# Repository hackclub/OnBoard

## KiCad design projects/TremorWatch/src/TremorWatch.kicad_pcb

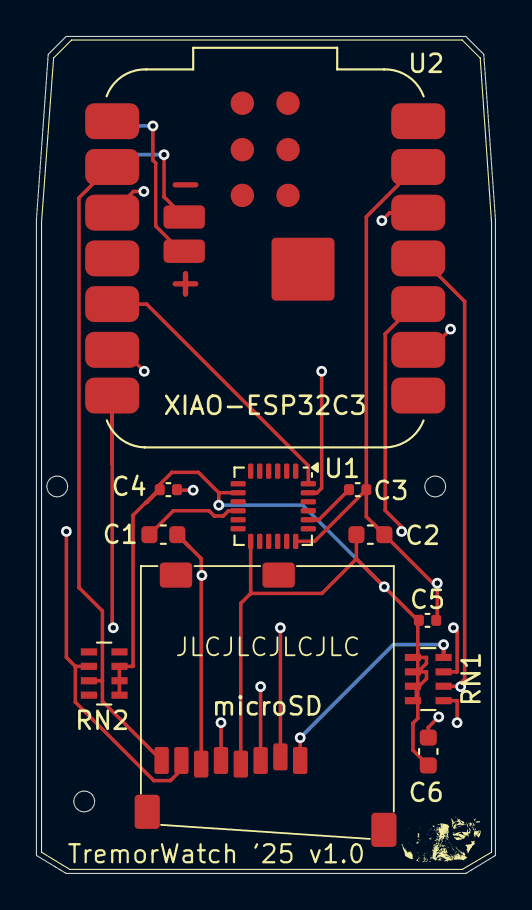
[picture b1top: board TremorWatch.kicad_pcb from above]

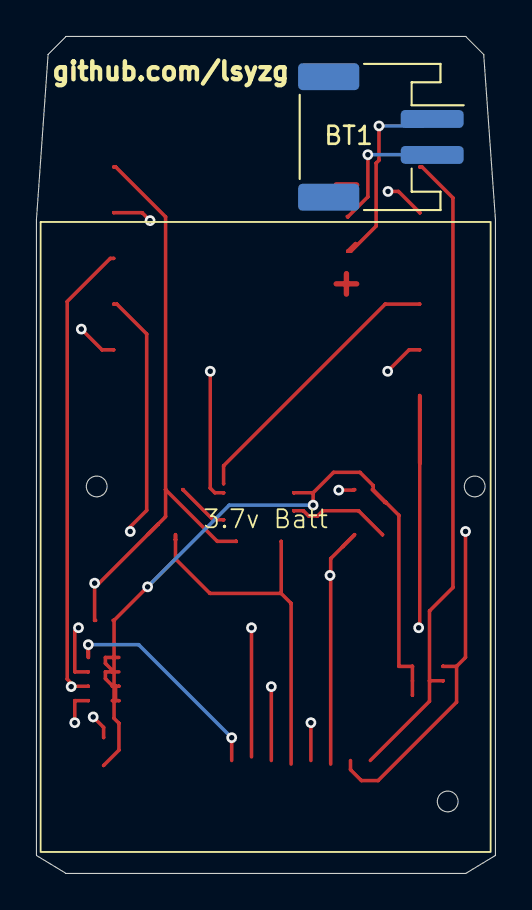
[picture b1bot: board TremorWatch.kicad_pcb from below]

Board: 4 copper layers, 25.5 x 46.5 mm, 14 parts (2 on the bottom side), 14 nets.

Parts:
3.7v Batt: bat_outline
BT1: Battery_Cell; JST_PH_S2B-PH-SM4-TB_1x02-1MP_P2.00mm_Horizontal
C1, C2, C6: 0.1uF; C_0603_1608Metric
C3: 2.2nF; C_0402_1005Metric
C4: 10nF; C_0402_1005Metric
C5: 10uF; C_0402_1005Metric
Intimidator: LOGO; timmy2
RN1, RN2: 4.7k; R_Array_Concave_4x0603
U1: MPU-6050; InvenSense_QFN-24_4x4mm_P0.5mm
U2: XIAO-ESP32C3; MCU_Seeed_ESP32C3
X1: microSD; MicroSD_Socket

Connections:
+3V3: C2.1, C4.1, C5.1, C6.1, RN1.1 (R1.1), RN1.2 (R2.1), RN1.3 (R3.1), RN1.4 (R4.1), RN2.1 (R1.1), RN2.2 (R2.1), RN2.3 (R3.1), U1.8 (VLOGIC), U1.13 (VDD), U2.12 (3V3), X1.4 (SD_VDD)
CLK: RN1.5 (R4.2), U2.9 (PA7_A8_D8_SCK), X1.5 (SCLK)
CS: RN1.7 (R2.2), U2.7 (PB08_A6_D6_TX), X1.2 (CS)
DAT1: RN2.7 (R2.2), U2.2 (PA4_A1_D1), X1.8 (DAT1)
DAT2: RN1.8 (R1.2), U2.3 (PA10_A2_D2), X1.1 (DAT2)
GND: C1.2, C2.2, C3.1, C4.2, C5.2, C6.2, U1.18 (GND), U2.13 (GND), X1.6 (GND@3)
MISO/SO: RN2.6 (R3.2), U2.10 (PA5_A9_D9_MISO), X1.7 (DATA_OUT)
MOSI/SI: RN1.6 (R3.2), U2.11 (PA6_A10_D10_MOSI), X1.3 (DATA_IN)
unnamed: BT1.1 (+), U2.16 (Power_+)
unnamed: BT1.2 (-), U2.17 (Power_-)
unnamed: C3.2, U1.20 (CPOUT)
unnamed: C1.1, U1.10 (REGOUT)
SCL: U1.23 (SCL), U2.6 (PA9_A5_D5_SCL)
SDA: U1.24 (SDA), U2.5 (PA8_A4_D4_SDA)

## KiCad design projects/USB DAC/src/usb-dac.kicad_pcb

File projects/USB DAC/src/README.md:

# usb-dac

USB DAC based on TI PCM2912A IC

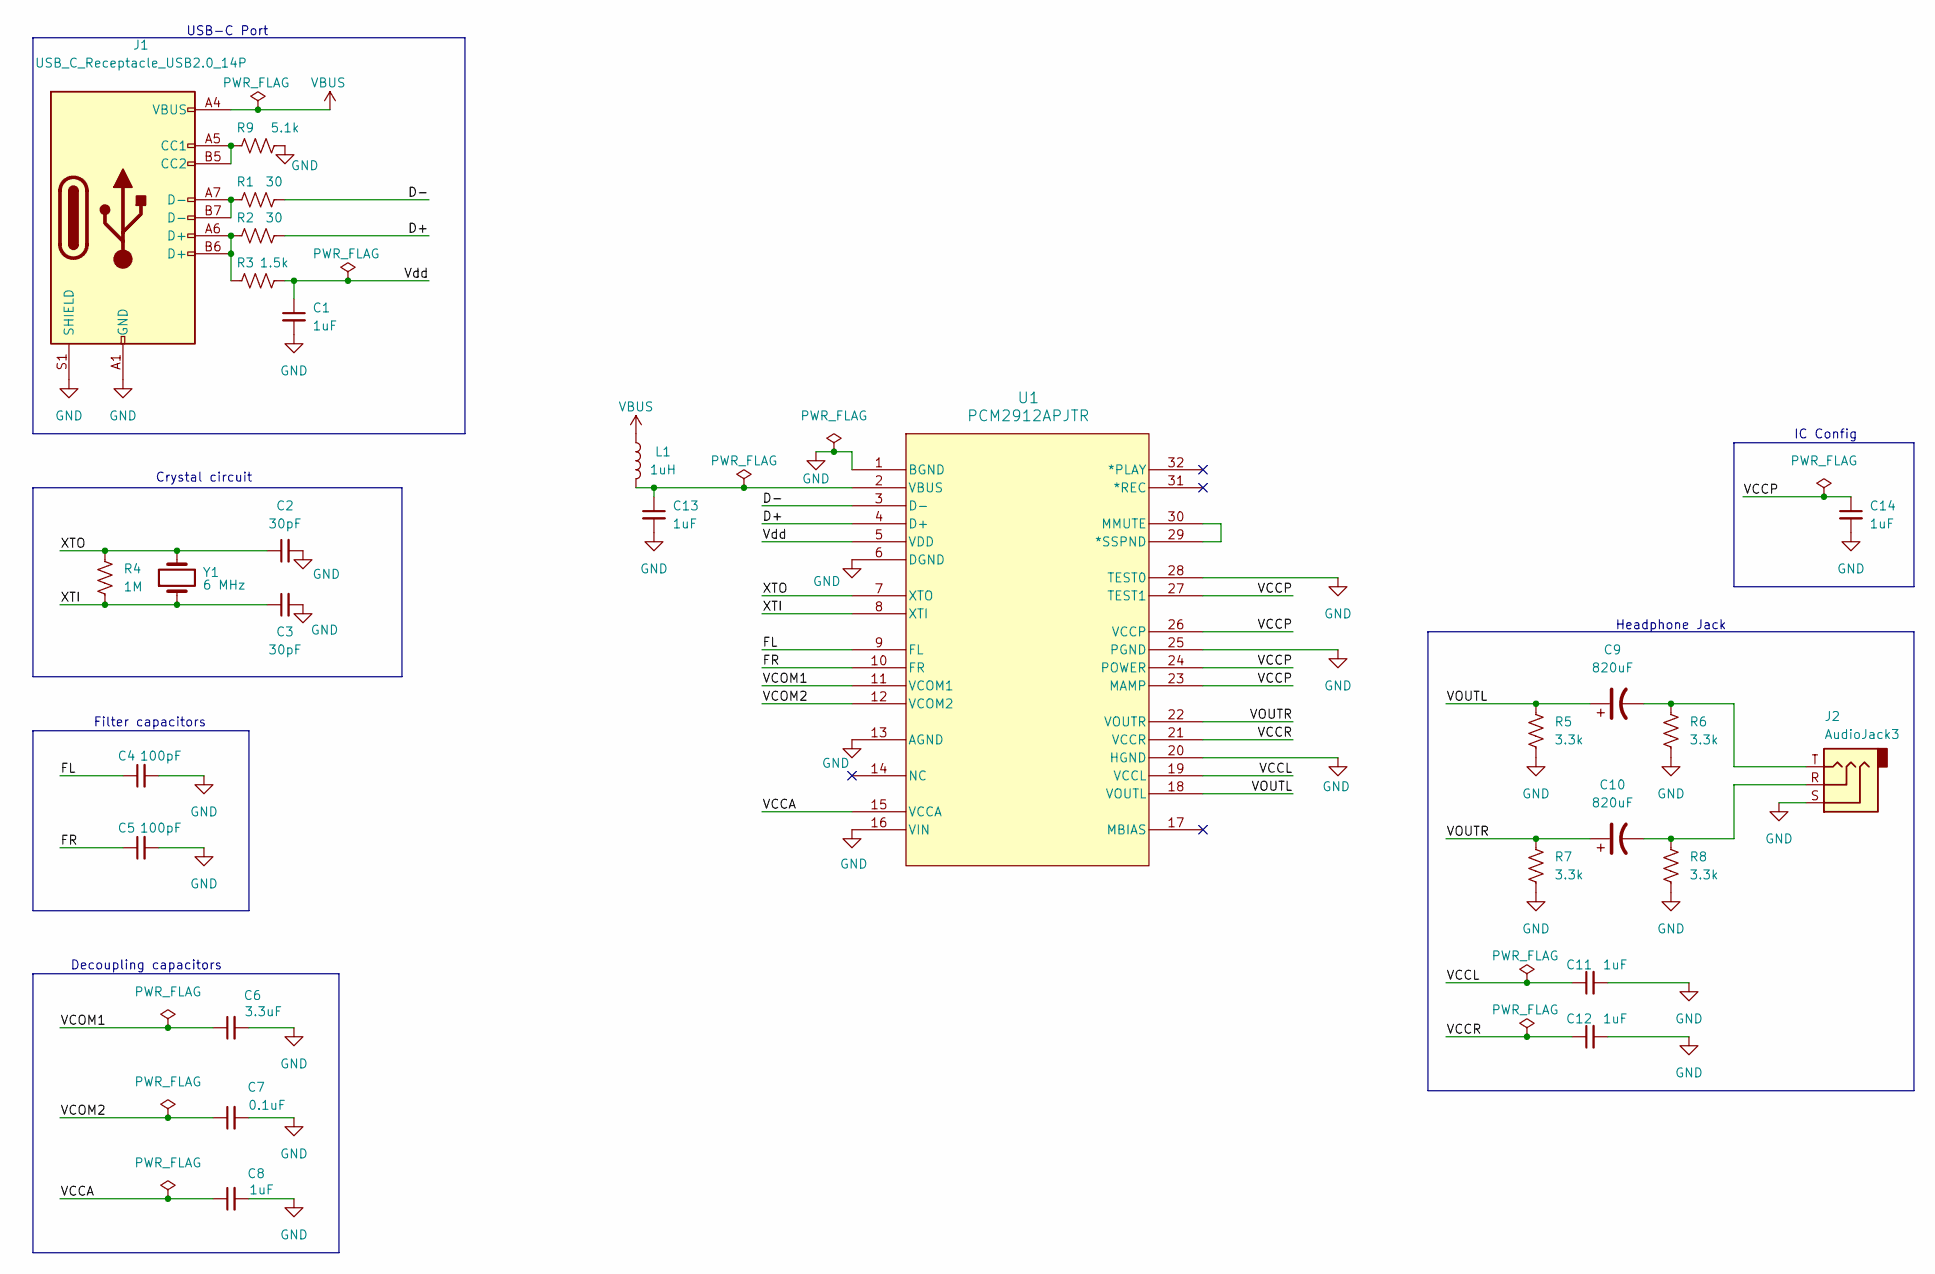
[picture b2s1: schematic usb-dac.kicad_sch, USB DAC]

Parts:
C1, C8, C11, C12, C13, C14: 1uF; C_Rect_L7.0mm_W2.0mm_P5.00mm; Mfr. # FG28X7R1E105KRT00
C2, C3: 30pF; C_Rect_L7.0mm_W2.0mm_P5.00mm; Mfr. # K300J10C0GF5UH5
C4, C5: 100pF; C_Rect_L7.0mm_W2.0mm_P5.00mm; Mfr. # XR501101K040HAND5P
C6: 3.3uF; C_Rect_L7.0mm_W2.0mm_P5.00mm; Mfr. # FA24X7R1E335KRU06
C7: 0.1uF; C_Rect_L7.0mm_W2.0mm_P5.00mm; Mfr. # K104K10X7RF5UH5
C9, C10: 820uF; CP_Radial_D8.0mm_P3.50mm; Mfr. # 6.3ZLH820MEFC8X11.5
J1: USB_C_Receptacle_USB2.0_14P; USB_C_Receptacle_GCT_USB4105-xx-A_16P_TopMnt_Horizontal; Mfr. # USB4085
J2: AudioJack3; Jack_3.5mm_CUI_SJ1-3523N_Horizontal; Mfr. # SJ1-3523N
L1: 1uH; L_Axial_L5.3mm_D2.2mm_P7.62mm_Horizontal_Vishay_IM-1; Mfr. # AICC-02-1R0M-T
R1, R2: 30; R_Axial_DIN0207_L6.3mm_D2.5mm_P10.16mm_Horizontal; Mfr. # CF14JT30R0
R3: 1.5k; R_Axial_DIN0207_L6.3mm_D2.5mm_P10.16mm_Horizontal; Mfr. # CFR-12JB-52-1K5
R4: 1M; R_Axial_DIN0207_L6.3mm_D2.5mm_P10.16mm_Horizontal; Mfr. # RNF18FTD1M00
R5, R6, R7, R8: 3.3k; R_Axial_DIN0207_L6.3mm_D2.5mm_P10.16mm_Horizontal; Mfr. # CFM14JT3K30
R9: 5.1k; R_Axial_DIN0207_L6.3mm_D2.5mm_P10.16mm_Horizontal; Mfr. # CF18JT5K10
U1: PCM2912APJTR; TQFP-32_7x7mm_P0.8mm; Mfr. # PCM2912APJTR
Y1: 6 MHz; Crystal_HC49-U_Vertical; Mfr. # ATS060

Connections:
/D+: R2.2, U1.4 (D+)
/D-: R1.2, U1.3 (D-)
/FL: C4.1, U1.9 (FL)
/FR: C5.1, U1.10 (FR)
/VCCA: C8.1, U1.15 (VCCA)
/VCCL: C11.1, U1.19 (VCCL)
/VCCP: C14.1, U1.23 (MAMP), U1.24 (POWER), U1.26 (VCCP), U1.27 (TEST1)
/VCCR: C12.1, U1.21 (VCCR)
/VCOM1: C6.1, U1.11 (VCOM1)
/VCOM2: C7.1, U1.12 (VCOM2)
/VOUTL: C9.1, R5.1, U1.18 (VOUTL)
/VOUTR: C10.1, R7.1, U1.22 (VOUTR)
/Vdd: C1.1, R3.2, U1.5 (VDD)
/XTI: C3.1, R4.2, U1.8 (XTI), Y1.1
/XTO: C2.1, R4.1, U1.7 (XTO), Y1.2
GND: C1.2, C2.2, C3.2, C4.2, C5.2, C6.2, C7.2, C8.2, C11.2, C12.2, C13.2, C14.2, J1.A1 (GND), J1.A12 (GND), J1.B1 (GND), J1.B12 (GND), J1.S1 (SHIELD), J2.S, R5.2, R6.2, R7.2, R8.2, R9.2, U1.1 (BGND), U1.6 (DGND), U1.13 (AGND), U1.16 (VIN), U1.20 (HGND), U1.25 (PGND), U1.28 (TEST0)
unnamed: C9.2, J2.T, R6.1
unnamed: C10.2, J2.R, R8.1
unnamed: J1.A5 (CC1), J1.B5 (CC2), R9.1
unnamed: J1.A6 (D+), J1.B6 (D+), R2.1, R3.1
unnamed: J1.A7 (D-), J1.B7 (D-), R1.1
unnamed: U1.29 (*SSPND), U1.30 (MMUTE)
unnamed: C13.1, L1.2, U1.2 (VBUS)
VBUS: J1.A4 (VBUS), J1.A9 (VBUS), J1.B4 (VBUS), J1.B9 (VBUS), L1.1

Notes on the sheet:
Filter capacitors
Headphone Jack
USB-C Port
Crystal circuit
Decoupling capacitors
IC Config

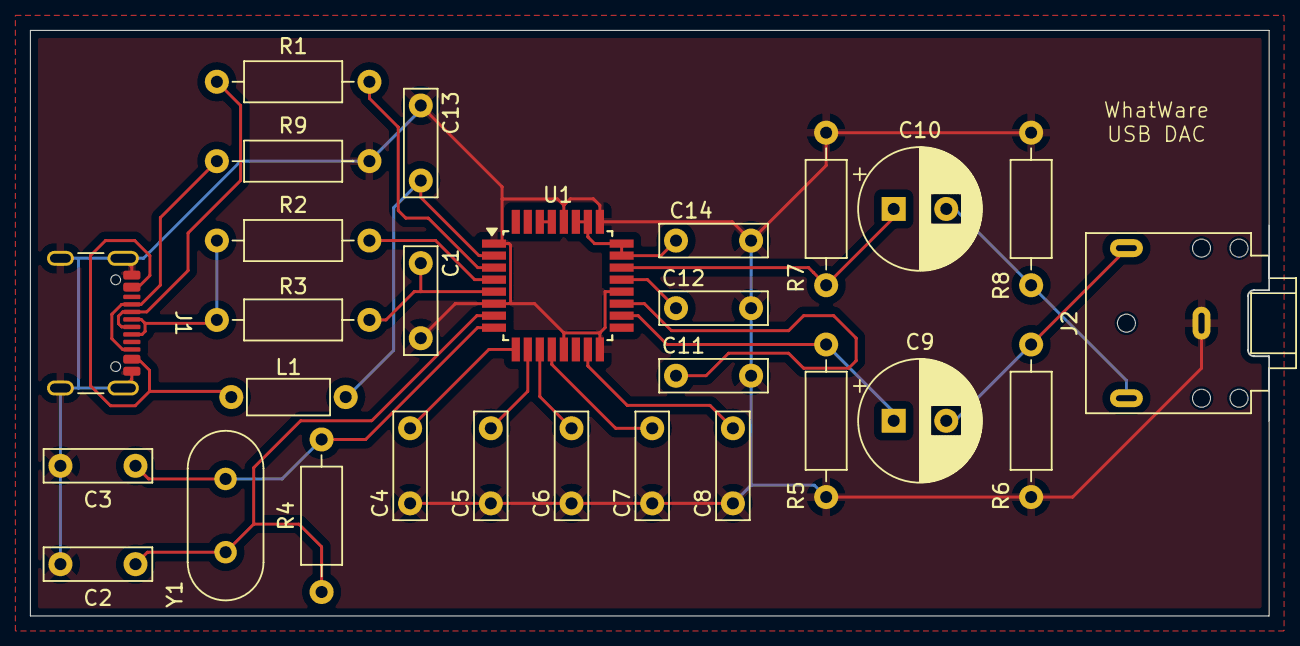
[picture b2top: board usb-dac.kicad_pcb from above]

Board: 2 copper layers, 82.5 x 39.0 mm, 28 parts (0 on the bottom side), 24 nets.

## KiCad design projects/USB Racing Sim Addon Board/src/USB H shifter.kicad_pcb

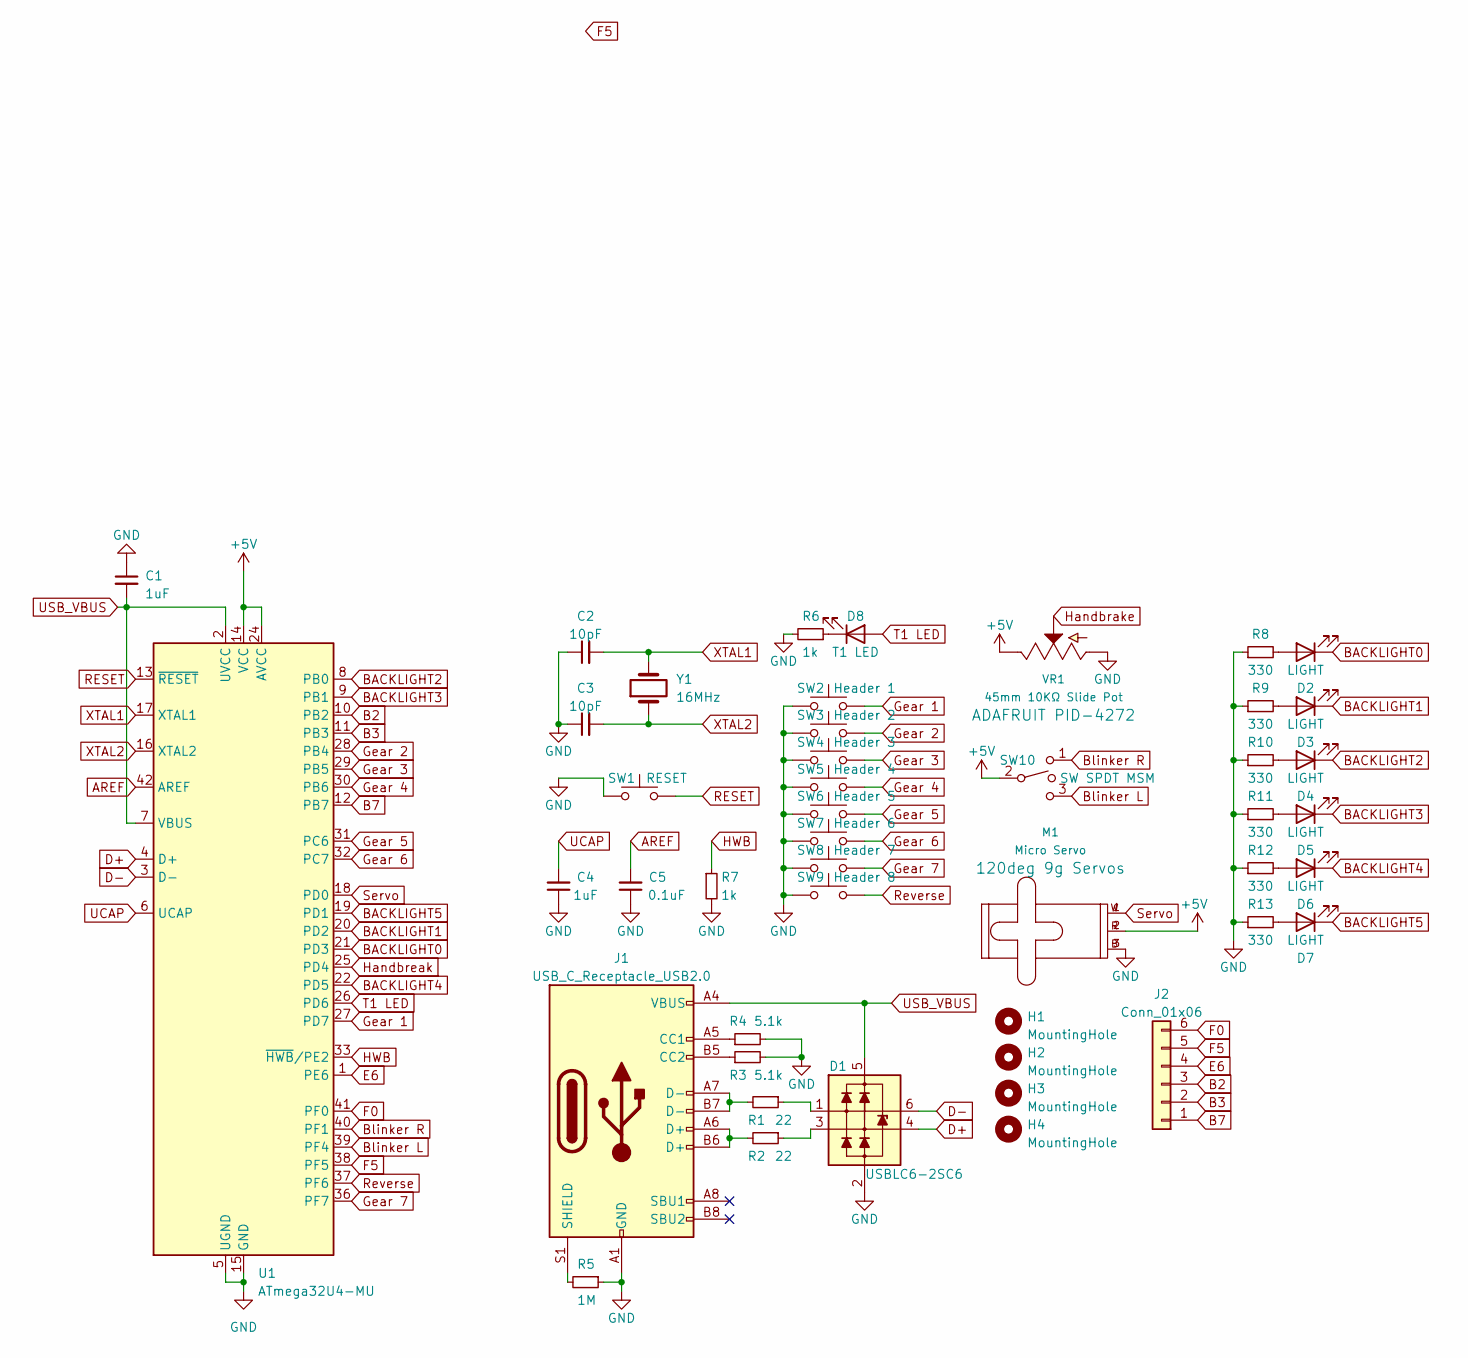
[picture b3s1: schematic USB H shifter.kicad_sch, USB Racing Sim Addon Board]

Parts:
C1, C4: 1uF; C_Disc_D4.3mm_W1.9mm_P5.00mm
C2, C3: 10pF; C_Disc_D3.0mm_W2.0mm_P2.50mm
C5: 0.1uF; C_Disc_D3.0mm_W2.0mm_P2.50mm
D1: USBLC6-2SC6; SOT-23-6
D2, D3, D4, D5, D6, D7: LIGHT; LED_D3.0mm
D8: T1 LED; LED_D3.0mm
H1, H2, H3, H4: MountingHole; MountingHole_2.2mm_M2
J1: USB_C_Receptacle_USB2.0; USB_C_Receptacle_Palconn_UTC16-G
J2: Conn_01x06; PinHeader_2x03_P2.54mm_Vertical
M1: Micro Servo; PinHeader_1x03_P2.54mm_Vertical
R1, R2: 22; R_0603_1608Metric
R3, R4: 5.1k; R_0603_1608Metric
R5: 1M; R_0603_1608Metric
R6, R7: 1k; R_0603_1608Metric
R8, R9, R10, R11, R12, R13: 330; R_0603_1608Metric
SW1: RESET; SW_PUSH_6mm
SW2: Header 1; PinHeader_1x02_P2.54mm_Vertical
SW3: Header 2; PinHeader_1x02_P2.54mm_Vertical
SW4: Header 3; PinHeader_1x02_P2.54mm_Vertical
SW5: Header 4; PinHeader_1x02_P2.54mm_Vertical
SW6: Header 5; PinHeader_1x02_P2.54mm_Vertical
SW7: Header 6; PinHeader_1x02_P2.54mm_Vertical
SW8: Header 7; PinHeader_1x02_P2.54mm_Vertical
SW9: Header 8; PinHeader_1x02_P2.54mm_Vertical
SW10: SW SPDT MSM; PinHeader_1x03_P2.54mm_Vertical
U1: ATmega32U4-MU; TQFP-44_10x10mm_P0.8mm
VR1: 45mm 10KΩ Slide Pot; PinHeader_1x03_P2.54mm_Vertical
Y1: 16MHz; Crystal_HC49-4H_Vertical

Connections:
+5V: M1.2 (V+), SW10.2, U1.14 (VCC), U1.24 (AVCC), U1.34 (VCC), U1.44 (AVCC), VR1.1 (E)
AREF: C5.2, U1.42 (AREF)
B2: J2.3, U1.10 (PB2)
B3: J2.2, U1.11 (PB3)
B7: J2.1, U1.12 (PB7)
BACKLIGHT0: D2.1 (K), U1.21 (PD3)
BACKLIGHT1: D3.1 (K), U1.20 (PD2)
BACKLIGHT2: D4.1 (K), U1.8 (PB0)
BACKLIGHT3: D5.1 (K), U1.9 (PB1)
BACKLIGHT4: D6.1 (K), U1.22 (PD5)
BACKLIGHT5: D7.1 (K), U1.19 (PD1)
Blinker L: SW10.3, U1.39 (PF4)
Blinker R: SW10.1, U1.40 (PF1)
D+: D1.4 (L2), U1.4 (D+)
D-: D1.6 (L1), U1.3 (D-)
E6: J2.4, U1.1 (PE6)
F0: J2.6, U1.41 (PF0)
F5: J2.5, U1.38 (PF5)
GND: C1.1, C2.1, C3.1, C4.1, C5.1, D1.2 (VN), J1.A1 (GND), J1.A12 (GND), J1.B1 (GND), J1.B12 (GND), M1.3 (GND), R3.2, R4.2, R5.1, R6.2, R7.2, R8.1, R9.1, R10.1, R11.1, R12.1, R13.1, SW1.1, SW2.1, SW3.1, SW4.1, SW5.1, SW6.1, SW7.1, SW8.1, SW9.1, U1.5 (UGND), U1.15 (GND), U1.23 (GND), U1.35 (GND), U1.43 (GND), VR1.3 (A)
Gear 1: SW2.2, U1.27 (PD7)
Gear 2: SW3.2, U1.28 (PB4)
Gear 3: SW4.2, U1.29 (PB5)
Gear 4: SW5.2, U1.30 (PB6)
Gear 5: SW6.2, U1.31 (PC6)
Gear 6: SW7.2, U1.32 (PC7)
Gear 7: SW8.2, U1.36 (PF7)
HWB: R7.1, U1.33 (~HWB/PE2)
Handbreak: U1.25 (PD4), VR1.2
unnamed: D1.1 (L1), R1.1
unnamed: D1.3 (L2), R2.1
unnamed: D2.2 (A), R8.2
unnamed: D3.2 (A), R9.2
unnamed: D4.2 (A), R10.2
unnamed: D5.2 (A), R11.2
unnamed: D6.2 (A), R12.2
unnamed: D7.2 (A), R13.2
unnamed: D8.1 (K), R6.1
unnamed: J1.A5 (CC1), R4.1
unnamed: J1.B5 (CC2), R3.1
unnamed: J1.A6 (D+), J1.B6 (D+), R2.2
unnamed: J1.A7 (D-), J1.B7 (D-), R1.2
unnamed: J1.S1 (SHIELD), R5.2
RESET: SW1.2, U1.13 (~RESET)
Reverse: SW9.2, U1.37 (PF6)
Servo: M1.1 (SIG), U1.18 (PD0)
T1 LED: D8.2 (A), U1.26 (PD6)
UCAP: C4.2, U1.6 (UCAP)
USB_VBUS: C1.2, D1.5 (VP), J1.A4 (VBUS), J1.A9 (VBUS), J1.B4 (VBUS), J1.B9 (VBUS), U1.2 (UVCC), U1.7 (VBUS)
XTAL1: C2.2, U1.17 (XTAL1), Y1.2
XTAL2: C3.2, U1.16 (XTAL2), Y1.1

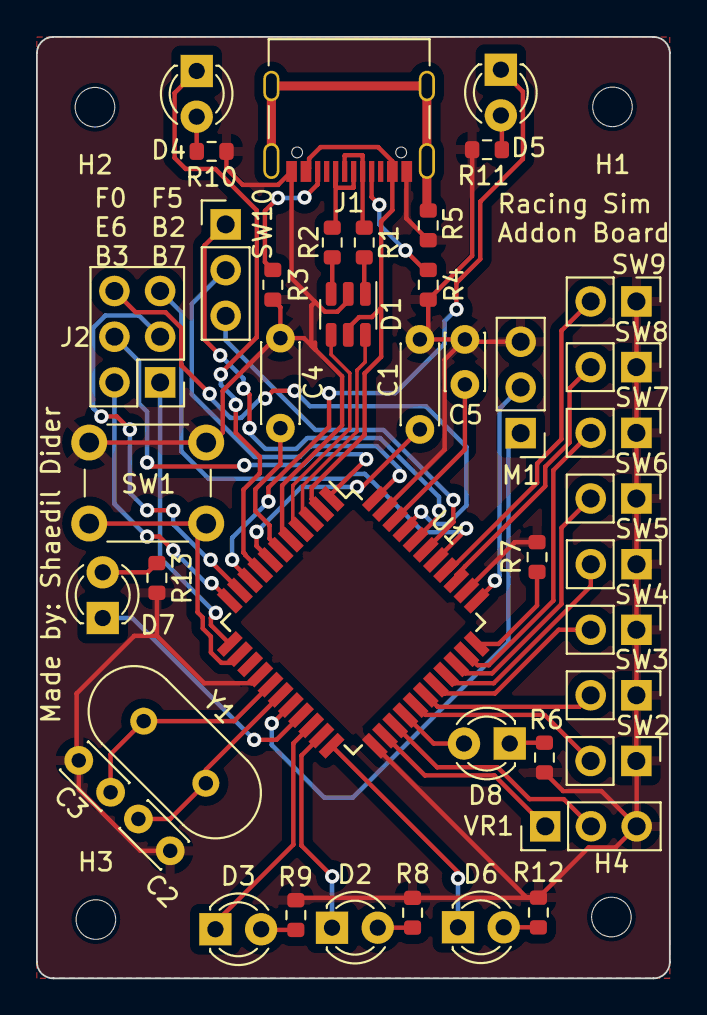
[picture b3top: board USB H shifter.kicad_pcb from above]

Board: 2 copper layers, 35.2 x 52.3 mm, 46 parts (0 on the bottom side), 50 nets.

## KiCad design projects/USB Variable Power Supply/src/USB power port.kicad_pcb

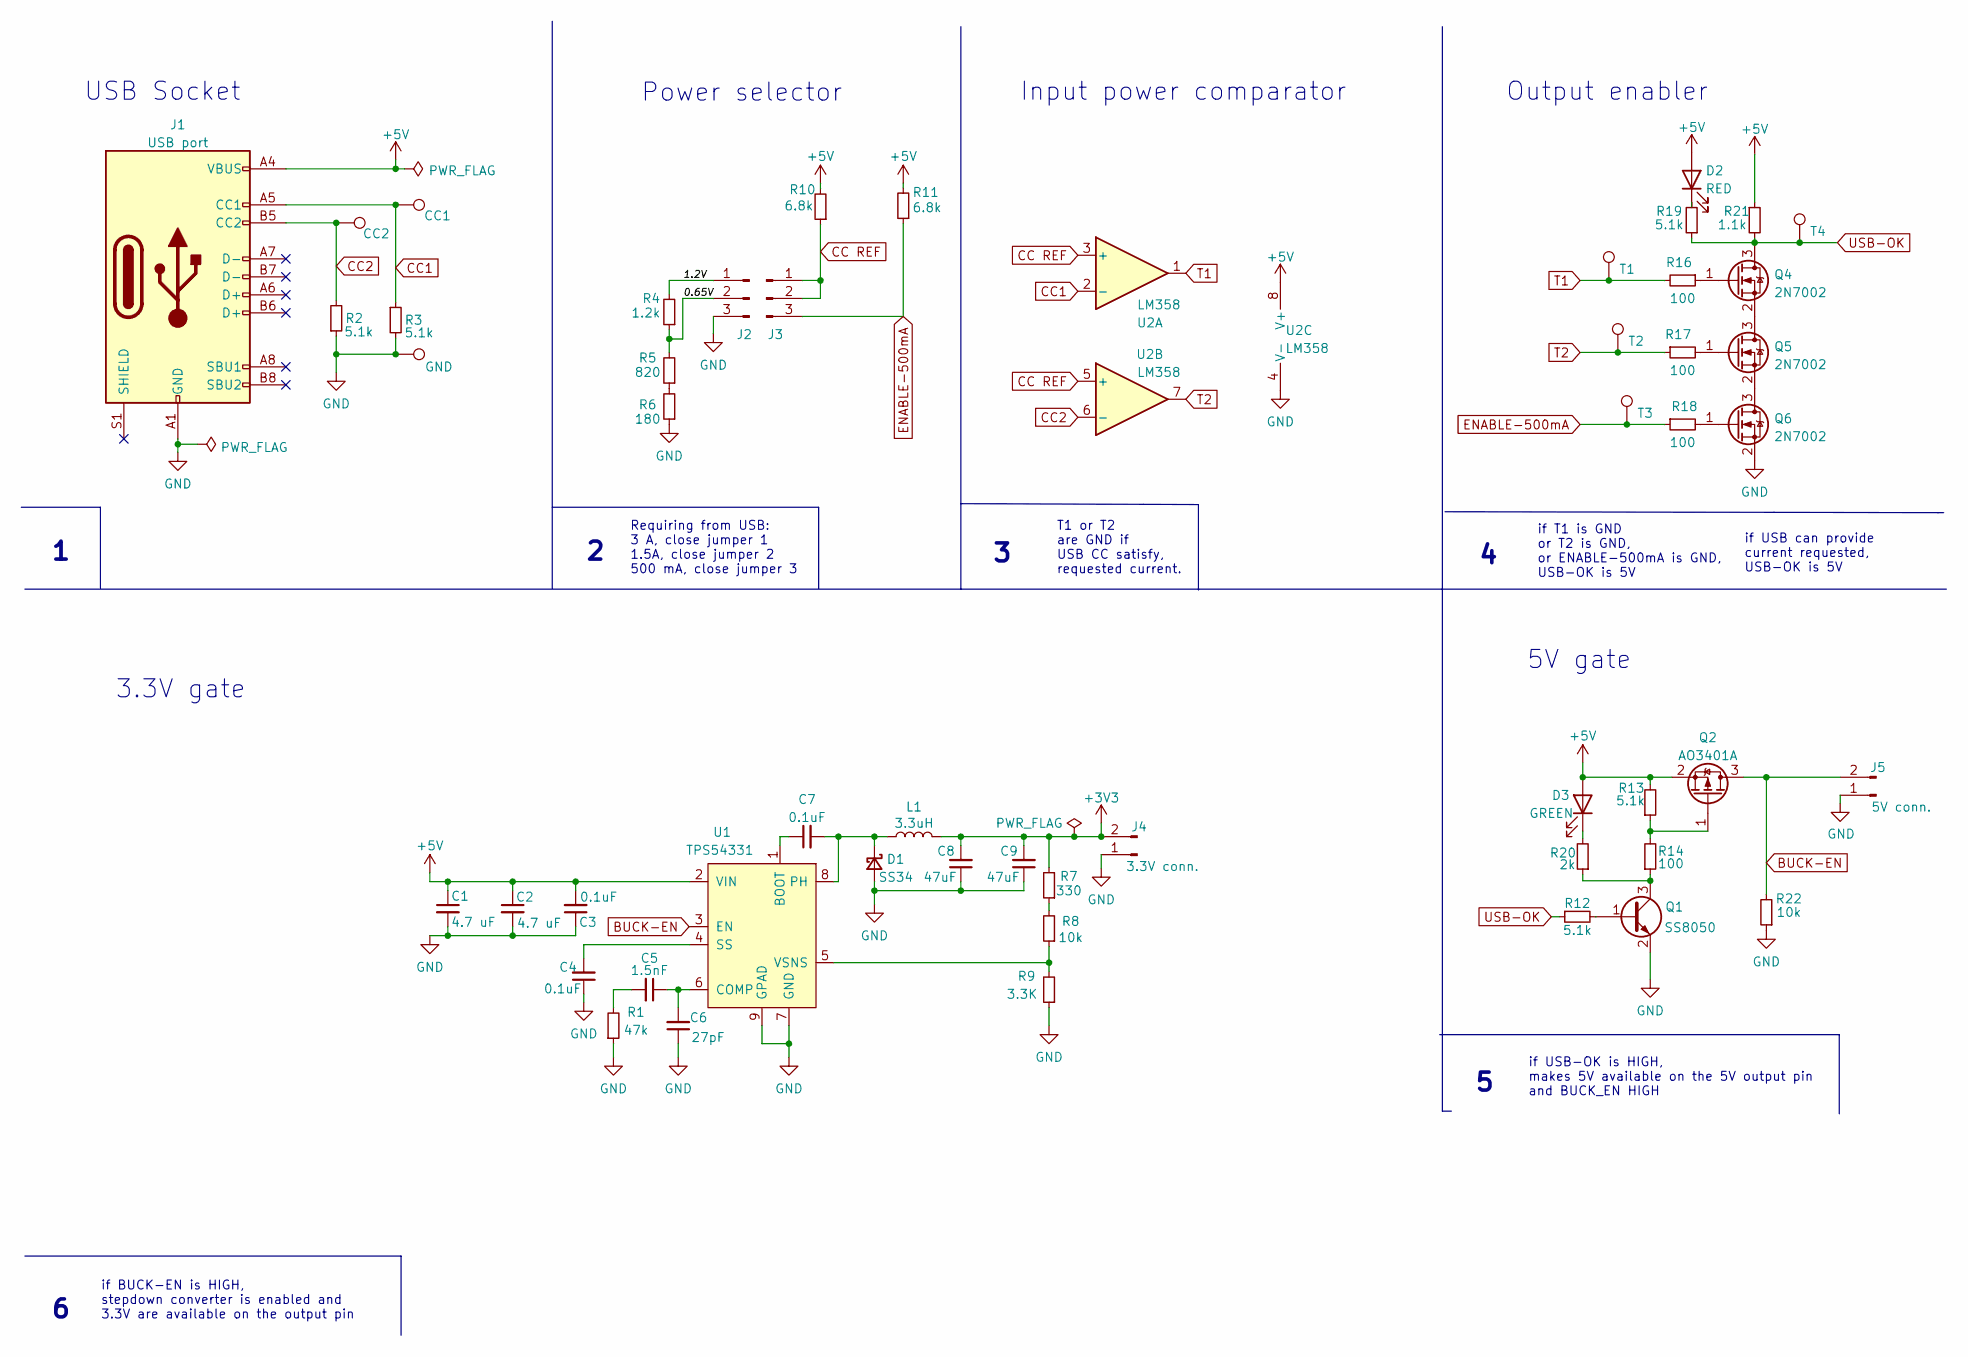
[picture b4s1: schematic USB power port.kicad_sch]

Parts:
C1, C2: 4.7 uF; C_1206_3216Metric; PartNo C29823
C3, C4, C7: 0.1uF; C_0603_1608Metric; PartNo C14663
C5: 1.5nF; C_0603_1608Metric; PartNo C1595
C6: 27pF; C_0603_1608Metric; PartNo C107045
C8, C9: 47uF; C_1206_3216Metric; PartNo C96123
D1: SS34; D_SMA; PartNo C8678
D2: RED; LED_0603_1608Metric; PartNo C2286
D3: GREEN; LED_0603_1608Metric; PartNo C72043
J1: USB port; USB_C_Receptacle_XKB_U262-16XN-4BVC11; PartNo C319148
J2, J3: Selector; PinHeader_1x03_P2.54mm_Vertical
J4: 3.3V conn.; PinHeader_1x02_P2.54mm_Vertical
J5: 5V conn.; PinHeader_1x02_P2.54mm_Vertical
L1: 3.3uH; MWSA0402; PartNo C285742
Q1: SS8050; SOT-23; PartNo C2150
Q2: AO3401A; SOT-23; PartNo C15127
Q4, Q5, Q6: 2N7002; SOT-23; PartNo C8545
R1: 47k; R_0603_1608Metric; PartNo C25819
R2, R3, R12, R13, R19: 5.1k; R_0603_1608Metric; PartNo C23186
R4: 1.2k; R_0603_1608Metric; PartNo C22765
R5: 820; R_0603_1608Metric; PartNo C23253
R6: 180; R_0603_1608Metric; PartNo C22828
R7: 330; R_0603_1608Metric; PartNo C23138
R8, R22: 10k; R_0603_1608Metric; PartNo C25804
R9: 3.3K; R_0603_1608Metric; PartNo C22978
R10, R11: 6.8k; R_0603_1608Metric; PartNo C23212
R14, R16, R17, R18: 100; R_0603_1608Metric; PartNo C22775
R20: 2k; R_0603_1608Metric; PartNo C22975
R21: 1.1k; R_0603_1608Metric; PartNo C22764
TP1: CC2; TestPoint_THTPad_D2.0mm_Drill1.0mm
TP2: CC1; TestPoint_THTPad_D2.0mm_Drill1.0mm
TP3: GND; TestPoint_THTPad_2.0x2.0mm_Drill1.0mm
TP4: T1; TestPoint_THTPad_D2.0mm_Drill1.0mm
TP5: T2; TestPoint_THTPad_D2.0mm_Drill1.0mm
TP6: T3; TestPoint_THTPad_D2.0mm_Drill1.0mm
TP7: T4; TestPoint_THTPad_D2.0mm_Drill1.0mm
U1: TPS54331; TI_SO-PowerPAD-8_ThermalVias; PartNo C9865
U2: LM358; SOIC-8_3.9x4.9mm_P1.27mm; PartNo C7950

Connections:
+3V3: C8.2, C9.2, J4.2, L1.2, R7.2
+5V: C1.1, C2.1, C3.2, D2.2 (A), D3.2 (A), J1.A4 (VBUS), J1.A9 (VBUS), J1.B4 (VBUS), J1.B9 (VBUS), Q2.2 (S), R10.2, R11.2, R13.2, R21.1, U1.2 (VIN), U2.8 (V+)
/0.65V: J2.2, R4.1, R5.2
/1.2V: J2.1, R4.2
BUCK-EN: J5.2, Q2.3 (D), R22.2, U1.3 (EN)
CC1: J1.A5 (CC1), R3.1, TP2.1, U2.2 (-)
CC2: J1.B5 (CC2), R2.2, TP1.1, U2.6 (-)
CC REF: J3.1, J3.2, R10.1, U2.3 (+), U2.5 (+)
ENABLE-500mA: J3.3, R11.1, R18.1, TP6.1
GND: C1.2, C2.2, C3.1, C4.1, C6.1, C8.1, C9.1, D1.2 (A), J1.A1 (GND), J1.A12 (GND), J1.B1 (GND), J1.B12 (GND), J2.3, J4.1, J5.1, Q1.2 (E), Q6.2 (S), R1.1, R2.1, R3.2, R6.1, R9.1, R22.1, TP3.1, U1.7 (GND), U1.9 (GPAD), U2.4 (V-)
unnamed: C5.2, R1.2
unnamed: C7.2, D1.1 (K), L1.1, U1.8 (PH)
unnamed: D2.1 (K), R19.2
unnamed: D3.1 (K), R20.2
unnamed: Q1.1 (B), R12.2
unnamed: Q1.3 (C), R14.1, R20.1
unnamed: Q2.1 (G), R13.1, R14.2
unnamed: Q4.1 (G), R16.1
unnamed: Q4.2 (S), Q5.3 (D)
unnamed: Q5.1 (G), R17.2
unnamed: Q5.2 (S), Q6.3 (D)
unnamed: Q6.1 (G), R18.2
unnamed: R5.1, R6.2
unnamed: R7.1, R8.2
unnamed: C7.1, U1.1 (BOOT)
unnamed: C5.1, C6.2, U1.6 (COMP)
unnamed: C4.2, U1.4 (SS)
unnamed: R8.1, R9.2, U1.5 (VSNS)
T1: R16.2, TP4.1, U2.1
T2: R17.1, TP5.1, U2.7
USB-OK: Q4.3 (D), R12.1, R19.1, R21.2, TP7.1

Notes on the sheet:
Input power comparator
if BUCK-EN is HIGH, stepdown converter is enabled and 3.3V are available on the output pin
if USB-OK is HIGH, makes 5V available on the 5V output pin and BUCK_EN HIGH
USB Socket
Output enabler
if USB can provide current requested, USB-OK is 5V
if T1 is GND or T2 is GND, or ENABLE-500mA is GND, USB-OK is 5V
T1 or T2 are GND if USB CC satisfy, requested current.
Power selector
Requiring from USB: 3 A, close jumper 1 1.5A, close jumper 2 500 mA, close jumper 3
5V gate
3.3V gate

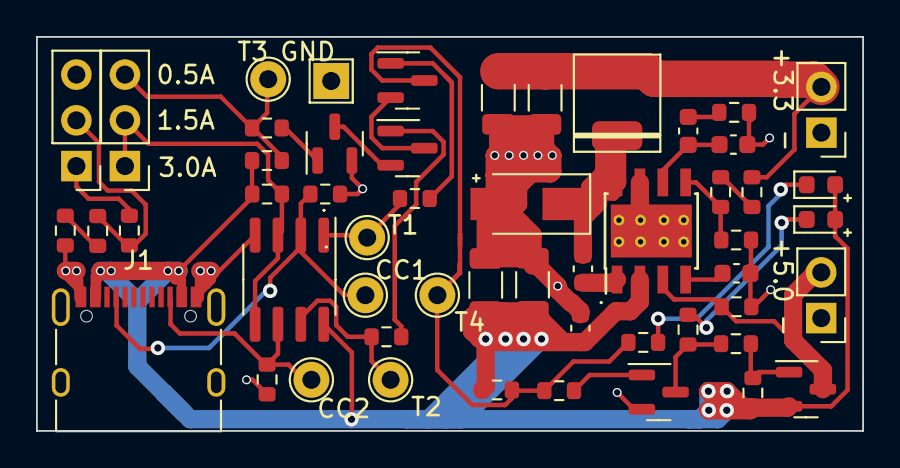
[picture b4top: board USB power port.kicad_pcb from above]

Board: 2 copper layers, 45.9 x 21.9 mm, 53 parts (0 on the bottom side), 31 nets.

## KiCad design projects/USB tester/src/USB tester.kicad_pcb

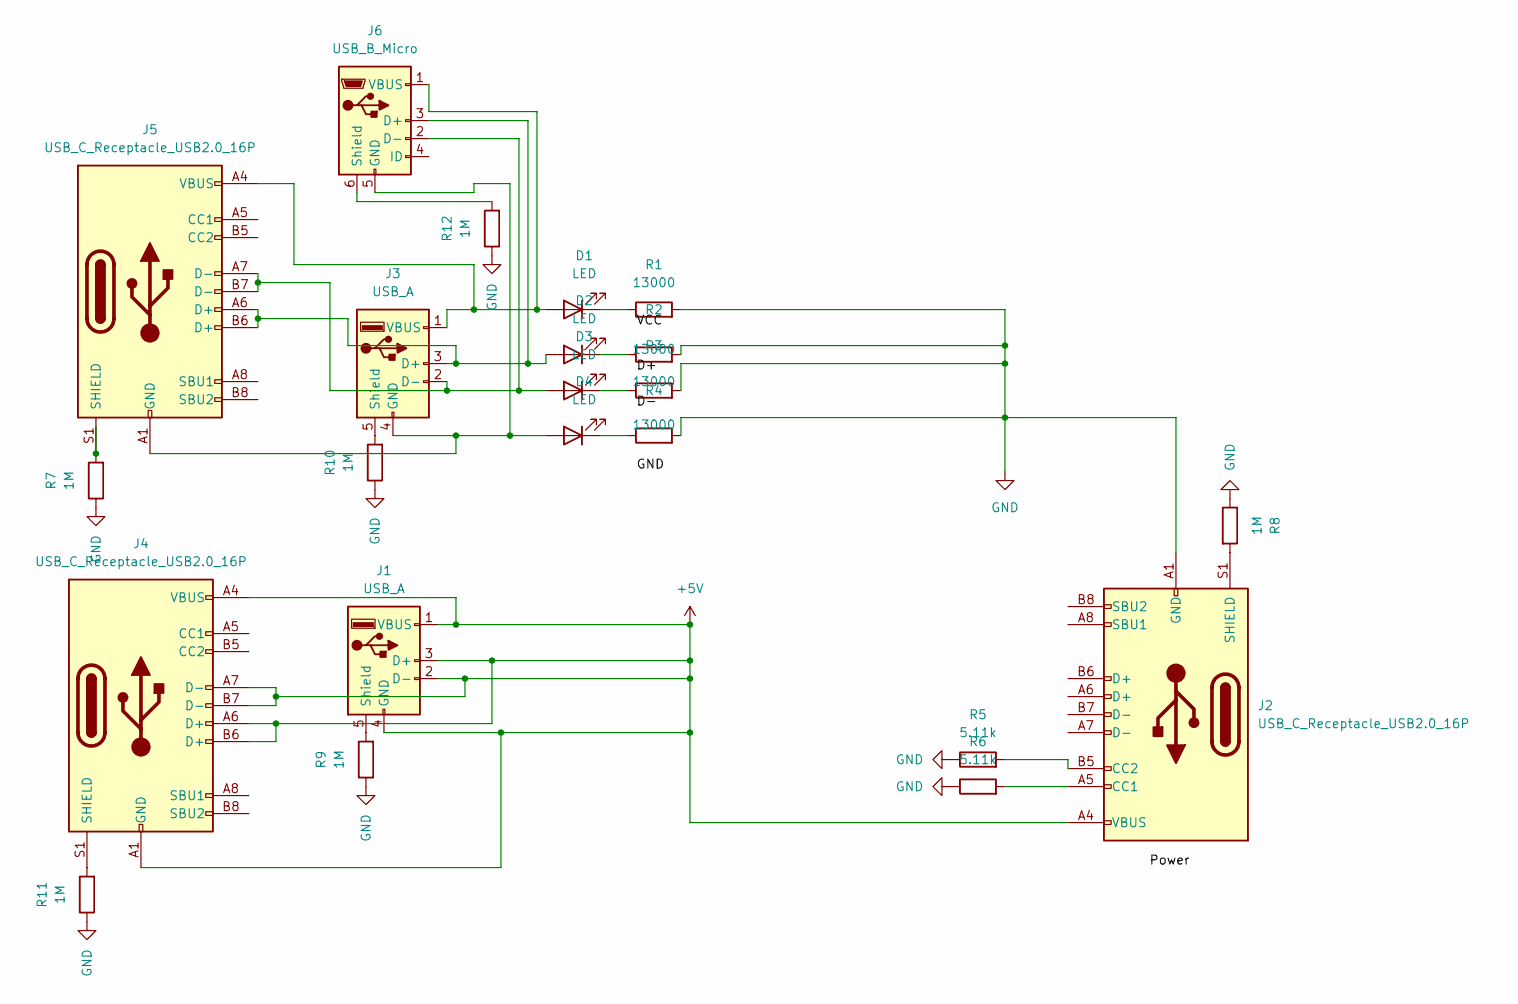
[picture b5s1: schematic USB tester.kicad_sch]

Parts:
D1, D2, D3, D4: LED; LED_1206_3216Metric
J1, J3: USB_A; USB_A_Receptacle_GCT_USB1046
J2, J4, J5: USB_C_Receptacle_USB2.0_16P; USB_C_Receptacle_G-Switch_GT-USB-7010ASV
J6: USB_B_Micro; USB_Micro-AB_Molex_47590-0001
R1, R2, R3, R4: 13000; R_0805_2012Metric
R5, R6: 5.11k; R_0805_2012Metric
R7, R8, R9, R10, R11, R12: 1M; R_0805_2012Metric

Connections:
+5V: J1.1 (VBUS), J1.2 (D-), J1.3 (D+), J1.4 (GND), J2.A4 (VBUS), J2.A9 (VBUS), J2.B4 (VBUS), J2.B9 (VBUS), J4.A1 (GND), J4.A4 (VBUS), J4.A6 (D+), J4.A7 (D-), J4.A9 (VBUS), J4.A12 (GND), J4.B1 (GND), J4.B4 (VBUS), J4.B6 (D+), J4.B7 (D-), J4.B9 (VBUS), J4.B12 (GND)
GND: J2.A1 (GND), J2.A12 (GND), J2.B1 (GND), J2.B12 (GND), R1.2, R2.2, R3.2, R4.2, R5.1, R6.1, R7.1, R8.1, R9.1, R10.1, R11.1, R12.1
unnamed: D1.2 (A), J3.1 (VBUS), J5.A4 (VBUS), J5.A9 (VBUS), J5.B4 (VBUS), J5.B9 (VBUS), J6.1 (VBUS)
unnamed: D1.1 (K), R1.1
unnamed: D2.2 (A), J3.3 (D+), J5.A6 (D+), J5.B6 (D+), J6.3 (D+)
unnamed: D2.1 (K), R2.1
unnamed: D3.2 (A), J3.2 (D-), J5.A7 (D-), J5.B7 (D-), J6.2 (D-)
unnamed: D3.1 (K), R3.1
unnamed: D4.2 (A), J3.4 (GND), J5.A1 (GND), J5.A12 (GND), J5.B1 (GND), J5.B12 (GND), J6.5 (GND)
unnamed: D4.1 (K), R4.1
unnamed: J1.5 (Shield), R9.2
unnamed: J2.A5 (CC1), R6.2
unnamed: J2.B5 (CC2), R5.2
unnamed: J2.S1 (SHIELD), R8.2
unnamed: J3.5 (Shield), R10.2
unnamed: J4.S1 (SHIELD), R11.2
unnamed: J5.S1 (SHIELD), R7.2
unnamed: J6.6 (Shield), R12.2

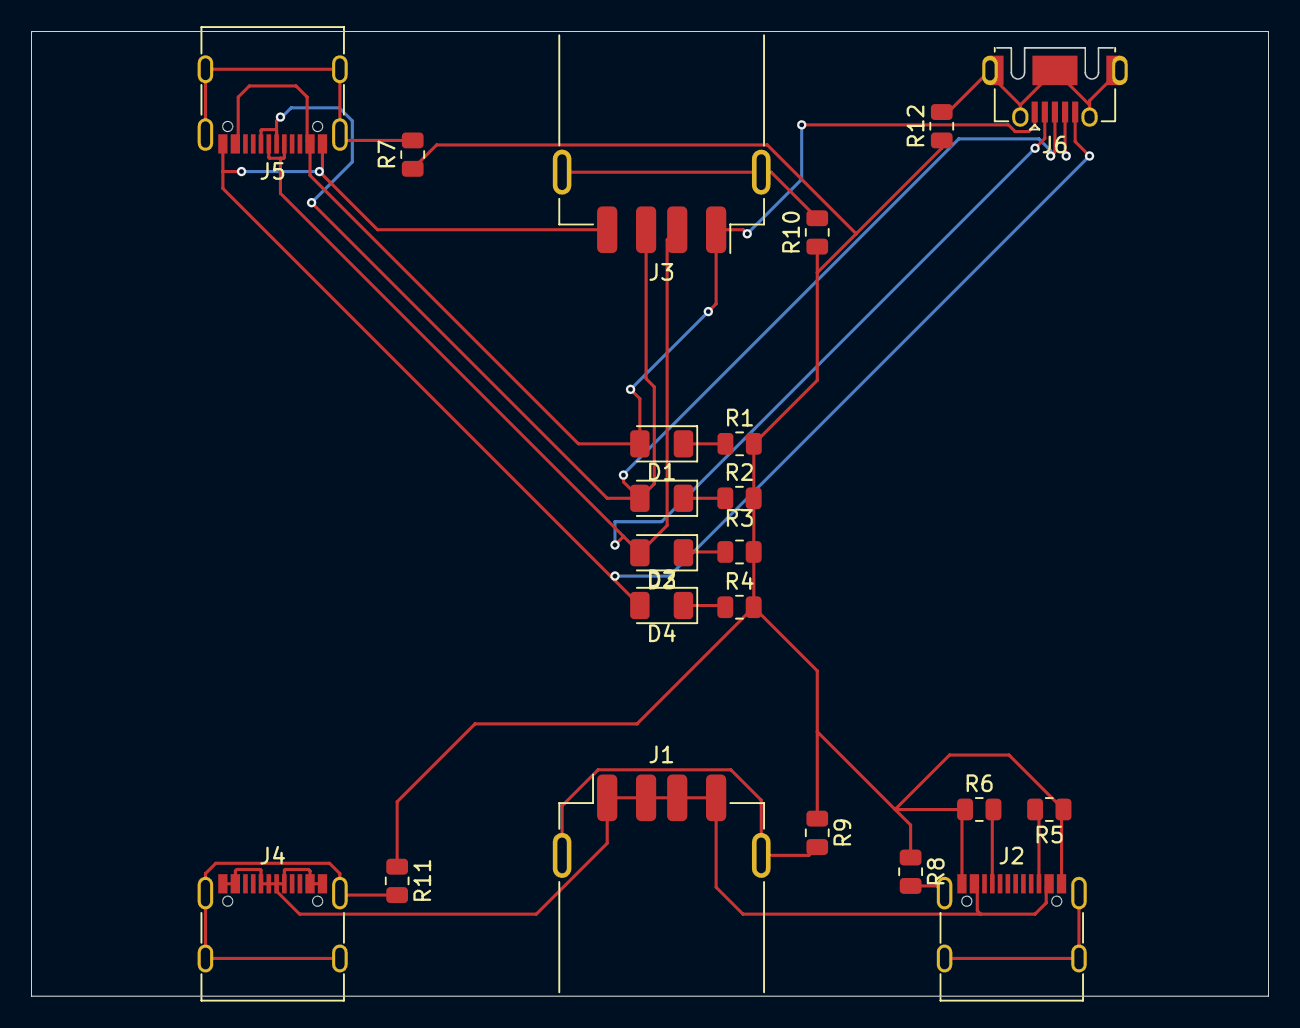
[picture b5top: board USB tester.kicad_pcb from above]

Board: 2 copper layers, 79.5 x 62.0 mm, 22 parts (0 on the bottom side), 18 nets.

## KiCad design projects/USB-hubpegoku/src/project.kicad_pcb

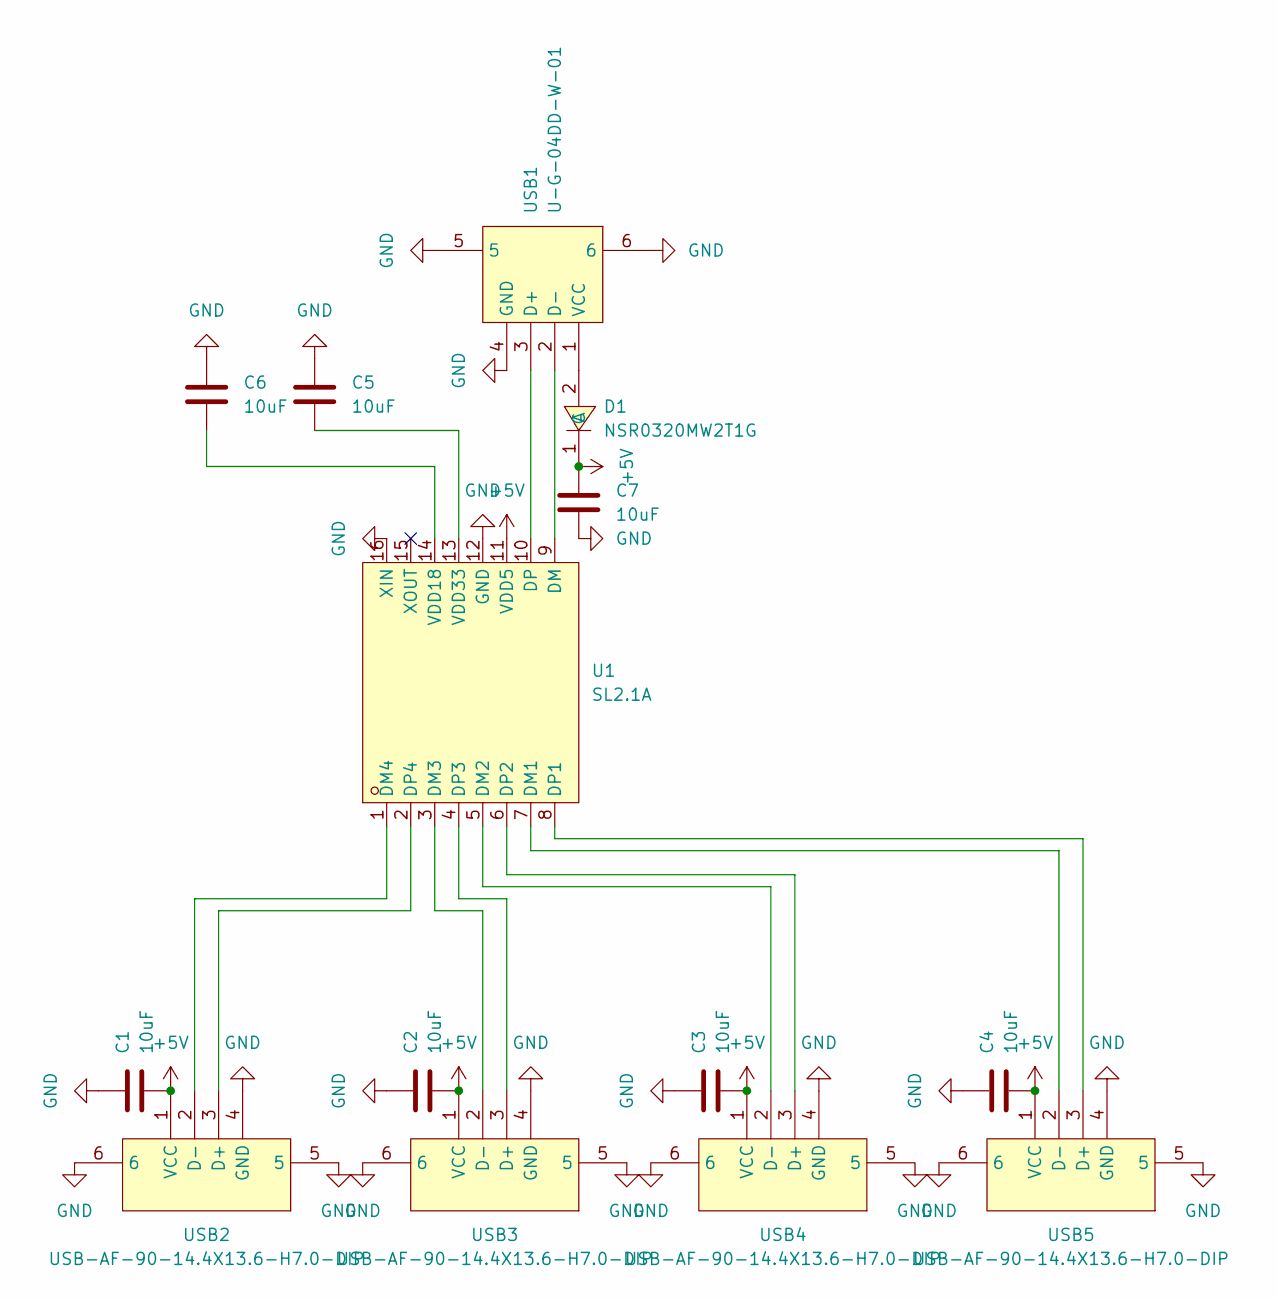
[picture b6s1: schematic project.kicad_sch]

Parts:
C1, C2, C3, C4, C5, C6, C7: 10uF; C_0603_1608Metric; LCSC C19702
D1: NSR0320MW2T1G; SOD-323_L1.8-W1.3-LS2.5-RD; LCSC Part C48192
U1: SL2.1A; SOP-16_L10.0-W3.9-P1.27-LS6.0-BL; LCSC Part C192893
USB1: U-G-04DD-W-01; USB-A-TH_U-G-04WD-W-01; LCSC Part C98125
USB2, USB3, USB4, USB5: USB-AF-90-14.4X13.6-H7.0-DIP; USB-A-TH_C46407; LCSC Part C46407

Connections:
+5V: C1.2, C2.2, C3.2, C4.2, C7.1, D1.1 (C), U1.11 (VDD5), USB2.1 (VCC), USB3.1 (VCC), USB4.1 (VCC), USB5.1 (VCC)
GND: C1.1, C2.1, C3.1, C4.1, C5.1, C6.1, C7.2, U1.12 (GND), U1.16 (XIN), USB1.4 (GND), USB1.5, USB1.6, USB2.4 (GND), USB2.5, USB2.6, USB3.4 (GND), USB3.5, USB3.6, USB4.4 (GND), USB4.5, USB4.6, USB5.4 (GND), USB5.5, USB5.6
unnamed: D1.2 (A), USB1.1 (VCC)
unnamed: U1.7 (DM1), USB5.2 (D-)
unnamed: U1.5 (DM2), USB4.2 (D-)
unnamed: U1.3 (DM3), USB3.2 (D-)
unnamed: U1.1 (DM4), USB2.2 (D-)
unnamed: U1.9 (DM), USB1.2 (D-)
unnamed: U1.8 (DP1), USB5.3 (D+)
unnamed: U1.6 (DP2), USB4.3 (D+)
unnamed: U1.4 (DP3), USB3.3 (D+)
unnamed: U1.2 (DP4), USB2.3 (D+)
unnamed: U1.10 (DP), USB1.3 (D+)
unnamed: C6.2, U1.14 (VDD18)
unnamed: C5.2, U1.13 (VDD33)
